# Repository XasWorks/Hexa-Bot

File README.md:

# Hexa-Bot

All required files, both .scad files for 3D Models aswell as the source files for the Arduino programming and the circuit plans for custom electronics (motor controller, special sensors, display etc.)

For documentation, see the "documentation" folder. Most importantly the scematics can be found under "KiCAD".

To program a robot, open Eclipse with working AVR Plugin, and "import existing project", with the folder being EclipseWS/Zephyr_Functional
The used PORTS can be changed inside the Code/System/Robot.h file.

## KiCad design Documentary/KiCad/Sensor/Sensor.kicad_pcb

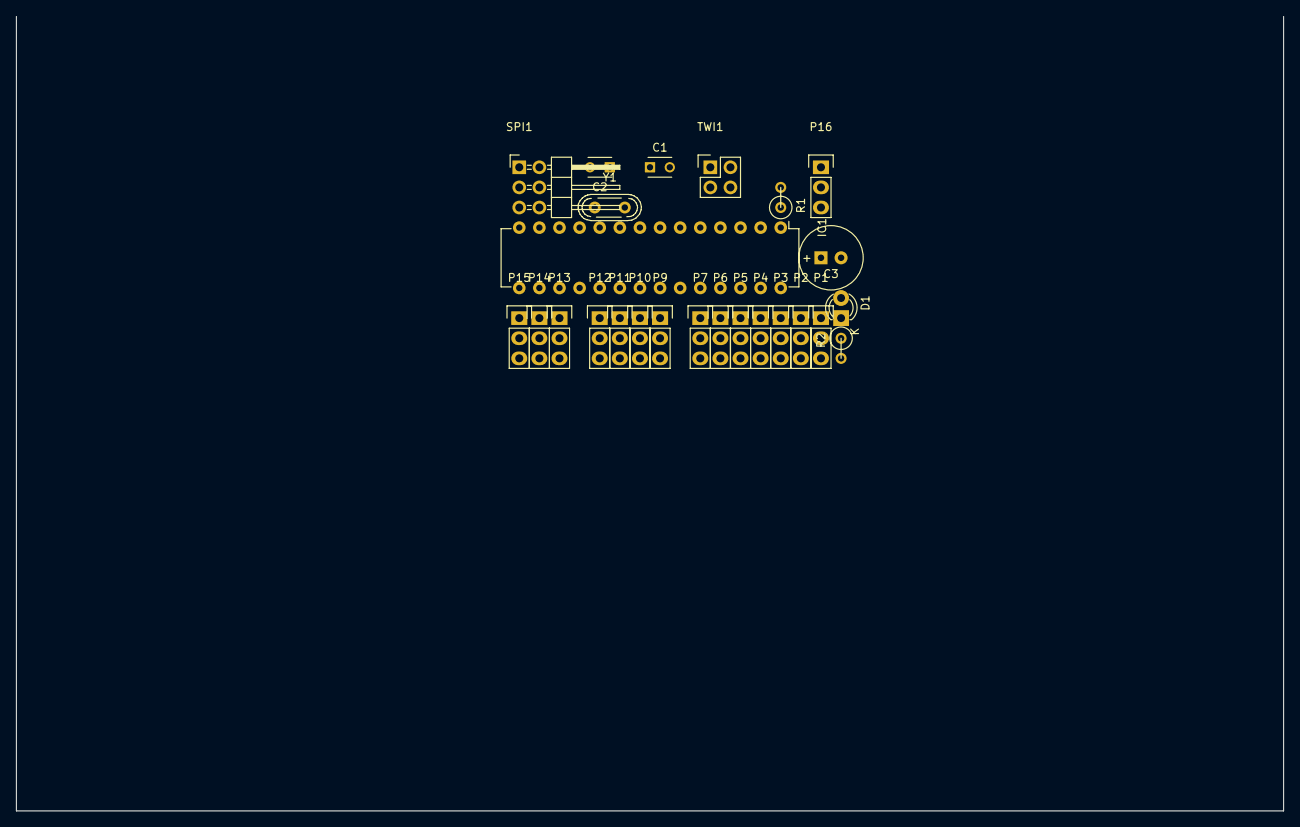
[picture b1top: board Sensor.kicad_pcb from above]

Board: 2 copper layers, 160.0 x 100.3 mm, 25 parts (0 on the bottom side), 26 nets, no tracks yet.

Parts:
C1, C2: C_Small; C_Disc_D3_P2.5
C3: CP; C1V8
D1: Led_Small; LED-3MM
IC1: ATMEGA8-P; DIP-28_W7.62mm
P1, P2, P3, P4, P5, P6, P7, P9, P10, P11, P12, P13, P14, P15, P16: CONN_01X03; Pin_Header_Straight_1x03
R1: R; R1
R2: R_Small; R1
SPI1: CONN_02X03; Pin_Header_Angled_2x03
TWI1: CONN_02X02; Pin_Header_Straight_2x02
Y1: Crystal; Crystal_HC52-U_Vertical

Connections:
+5V: C3.1, IC1.7, IC1.20, IC1.21, P1.2, P2.2, P3.2, P4.2, P5.2, P6.2, P7.2, P9.2, P10.2, P11.2, P12.2, P13.2, P14.2, P15.2, P16.2, R1.2, SPI1.2, TWI1.4
/MISO: IC1.18, SPI1.1
/MOSI: IC1.17, P16.1, SPI1.4
/PB0: IC1.14, P13.1
/PB1: IC1.15, P14.1
/PB2: IC1.16, P15.1
/PC0: IC1.23, P9.1
/PC1: IC1.24, P10.1
/PC2: IC1.25, P11.1
/PC3: IC1.26, P12.1
/PD0: IC1.2, P1.1
/PD1: IC1.3, P2.1
/PD2: IC1.4, P3.1
/PD3: IC1.5, P4.1
/PD4: IC1.6, P5.1
/PD5: IC1.11, P6.1
/PD6: IC1.12, P7.1
/PD7: D1.2, IC1.13
/RST: IC1.1, R1.1, SPI1.5
/SCK: IC1.19, SPI1.3
/SCL: IC1.28, TWI1.2
/SDA: IC1.27, TWI1.1
GND: C1.1, C2.2, C3.2, IC1.8, IC1.22, P1.3, P2.3, P3.3, P4.3, P5.3, P6.3, P7.3, P9.3, P10.3, P11.3, P12.3, P13.3, P14.3, P15.3, P16.3, R2.2, SPI1.6, TWI1.3
unnamed: C1.2, IC1.9, Y1.2
unnamed: C2.1, IC1.10, Y1.1
unnamed: D1.1, R2.1

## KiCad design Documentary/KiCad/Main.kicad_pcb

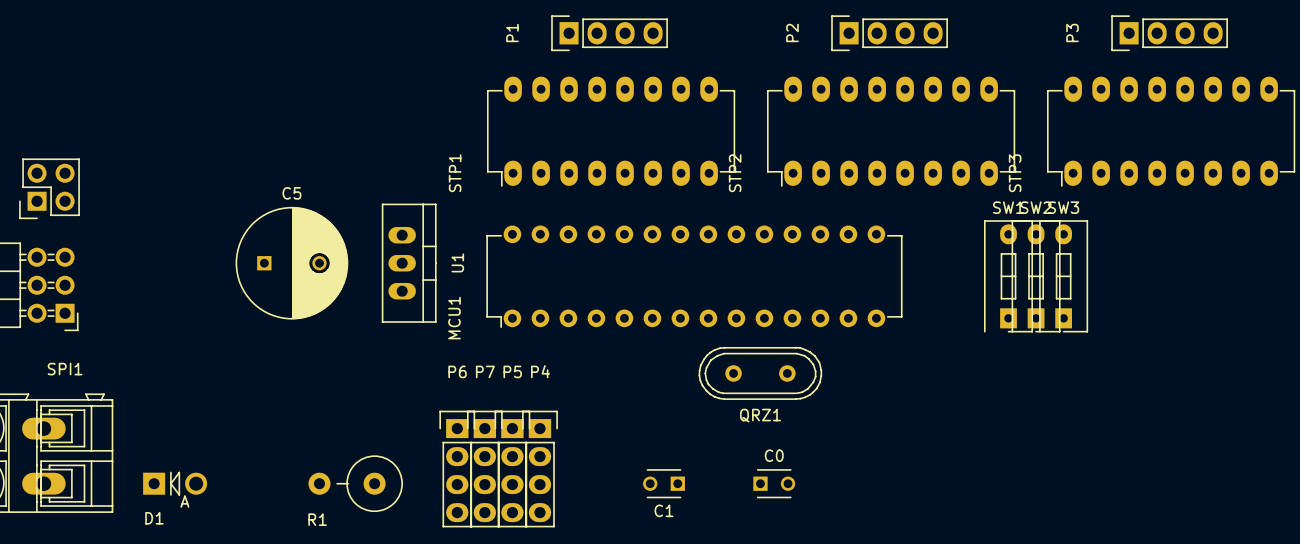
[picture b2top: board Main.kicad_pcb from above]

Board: 32 copper layers, 24 parts (0 on the bottom side), 40 nets, no tracks yet.

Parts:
C0, C1: C_Small; C_Disc_D3_P2.5
C5: CP; C_Radial_D10_L13_P5
D1: D_Small; Diode_DO-41_SOD81_Vertical_AnodeUp
MCU1: ATMEGA328-P; DIP-28_W7.62mm
P1, P2, P3: CONN_01X04; Pin_Header_Straight_1x04
P4, P5, P6, P7: CONN_01X03; Pin_Header_Straight_1x04
P8: CONN_02X02; Pin_Header_Straight_2x02
P9: CONN_01X02; AK300-2
QRZ1: Crystal; Crystal_HC49-U_Vertical
R1: 1M; Resistor_Vertical_RM5mm
SPI1: CONN_02X03; Pin_Header_Angled_2x03
STP1, STP2, STP3: A4988; DIP-16_W7.62mm_LongPads
SW1, SW2, SW3: SPST; SW_DIP_x1_Slide
U1: 7805; TO-220_Neutral123_Vertical

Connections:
+5V: C5.1, MCU1.7, MCU1.20, MCU1.21, P4.2, P5.2, P6.2, P7.2, P8.2, R1.2, SPI1.2, STP1.10, STP2.10, STP3.10, U1.3
+12V: P9.2, STP1.16, STP2.16, STP3.16, U1.1
/DR0: MCU1.3, STP1.8
/DR1: MCU1.5, STP2.8
/DR2: MCU1.11, STP3.8
/MISO: MCU1.18, SPI1.1
/MOSI: MCU1.17, SPI1.4
/MS0: STP1.2, STP2.2, STP3.2, SW1.2
/MS1: STP1.3, STP2.3, STP3.3, SW2.2
/MS2: STP1.4, STP2.4, STP3.4, SW3.2
/RST: MCU1.1, R1.1, SPI1.5
/SCK: MCU1.19, SPI1.3
/SCL: MCU1.28, P8.4
/SDA: MCU1.27, P8.3
/SN0: MCU1.23, P4.1
/SN1: MCU1.24, P5.1
/SN2: MCU1.25, P6.1
/SN3: MCU1.26, P7.1
/ST0: MCU1.2, STP1.7
/ST1: MCU1.4, STP2.7
/ST2: MCU1.6, STP3.7
GND: C0.1, C1.2, C5.2, D1.2, MCU1.8, MCU1.22, P4.3, P5.3, P6.3, P7.3, P8.1, SPI1.6, STP1.9, STP1.15, STP2.9, STP2.15, STP3.9, STP3.15, SW1.1, SW2.1, SW3.1, U1.2
unnamed: C0.2, MCU1.10, QRZ1.1
unnamed: C1.1, MCU1.9, QRZ1.2
unnamed: D1.1, P9.1
unnamed: P1.1, STP1.14
unnamed: P1.2, STP1.13
unnamed: P1.3, STP1.12
unnamed: P1.4, STP1.11
unnamed: P2.1, STP2.14
unnamed: P2.2, STP2.13
unnamed: P2.3, STP2.12
unnamed: P2.4, STP2.11
unnamed: P3.1, STP3.14
unnamed: P3.2, STP3.13
unnamed: P3.3, STP3.12
unnamed: P3.4, STP3.11
unnamed: STP1.5, STP1.6
unnamed: STP2.5, STP2.6
unnamed: STP3.5, STP3.6

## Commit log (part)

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2010-01-01 Changed drive preference to move along right, not left.
2015-09-16 Initial commit, the first HexGrid outline finished
2015-09-16 There we go. Actual Commit, including all the files (instead of empty push *sigh*)
2015-09-16 Removed that one weird HexGrid.scad directly in the master directory. Why.
2015-09-17 Added the first (and hopefully last) version of the .scad file used for creating the subwheels of a Omni-wheel. All functions are commented, no need for later commenting.
2015-09-17 Finalised version of the omni-wheel .scad!
2015-09-17 Fine-tuned the Filament-Axis holes.
    Values are now: 2.25 for tight-fitting and 2.4 for loosely-fitting.
2015-09-19 Filament axis hole now is only tighter towards end of the wheel.
    This should make it much more easy to insert the filament and fix the wheels in place. Glue is still recommended.
    Also, the hole diameter now is designed for toothpicks!!!
2015-09-20 Optimised and changed a few things.
    Nothing worth noting, mostly making the holes more fitting!
2015-09-20 Nearly done ...
2015-09-21 Finalised the alternate design!
    Added connectors for the subwheels, changed up the center piece a bit to use up less filament and all that.
2015-09-23 Complete redesign! My gosh, everything has changed. The central cylinder now is split into two symmetric parts that have to be glued together This SHOULD fix printing problems and allow for connector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
2015-09-25 Redid the Center piece code, much cleaner now.
    Redid lots of things, most noticably the center piece.
    This also includes stuff and configurability. Lots of things were replaced by variables and should be MUCH easier to configure now.
2015-09-26 Even more configurability! Seriously, round about now almost everything can be configured with a variable. //No warnings will be issued if the variables are set wrong!! //
2015-09-27 Added subwheel overlap value. This should allow for smoother running, as the subwheels overlap for a short amount of time, allowing the wheels to have a smoother run.
2015-10-01 First improvements on the Hexagonal Structure system!
    Made a few things accessible through variables, will change up the actual values and stuff later on.
2015-10-03 Added the eclipse workspace, and started LCD Driver!!
2015-10-04 Experimenting with C++ classes (LEDPWM)
    This first experiment is meant simply to test out a few things I want to have for a private, non-related project.
    However, the advances in understanding C++ will greatly help me out in continuing with this system.
2015-10-05 Ah ... Forgot the LED PWM Files
2015-10-06 Whoop Whoop, base stepper code fully functional!
    That is AWESOME, as now those dang steppers can be used perfectly!
    Also, the base frame code can easily be extended by overwriting the basic classes, or the stepper itself can be tested and moved about with the implemented function!
2015-10-07 Improvements to the ISR Step speed calculation.
    I still have to play around with the system to find out the best way to calculate and step the motors.
    Right now it fails to go over a specific amount (ISR Frequency < Stepping speed), but this can be resolved by making the ISR faster.
2015-10-08 First tries for accelleration!
2015-10-08 First complex driver motor calculation classes.
    And it already supports moving itself a specified amount of steps!!
2015-10-08 Some last minute testing and messing around.
2015-10-15 Untested optimisations for mov. cal and refined and strenghtened OmniWheel Bases.
2015-10-24 Small fix for the Stepper Motor connecting plate (size)
2015-10-25 Fixes to the new hexgrid system
2015-11-10 Start of code rewrite, implementation of interface "Movable"
2015-11-10 Commenting for class "Movable"
2015-11-15 Finished the last elemets of the new stepper system.
2015-11-16 Moved all the important movement files to a separate folder.
2015-11-17 First implementations of the I2C important buffers
2015-11-19 Began redesigning the motor hex system, added base-plate with integrated motor holder.
2015-11-21 Tried to fix the hexGrid system, and kinda managed that + First attempt at the base plate.
2015-11-21 Comments. Lots of them. And a clearer, cleaner code. Finally.
2015-11-22 Small fixes to the stepper motor system.
2015-11-22 Final changes to the Hex Grid structure!
2015-11-22 Small tweaks to the OmniWheel
2015-11-23 Tiny fine-tuning to the Omniwheels
2015-11-27 Small important fix to the XY-Coordinate to TranslativeStepper-Coordinate calculation
2015-11-27 Small in-between test
2015-11-27 Final commit before merge
2015-11-28 Repositioned the NewHexGrid library
2015-12-02 Small tweaks to the distancer
2015-12-03 Added a LF Sensor mount for the System.
2015-12-05 Implementation of a electronics holder and other various fixes
2015-12-08 Interim commit before master merge
2015-12-08 Cleanup of .gitignore Files.
2015-12-09 Correcting some small values
2015-12-11 Final tweaks to the LF-Shielding
2015-12-12 Small tweak for the sensors (Scaling)
2015-12-13 +Smaller fixes +Added comments and port specifications -Deleted led support (cleaned up)
2015-12-14 Implementation of I2CJobs
2015-12-15 First attempts towards I2CJob
2015-12-16 Small tweaks to the LF
2015-12-20 v0.1 I2C - Master only!
2016-01-03 First verion of a proper LF Class This new class system should make working with Line Following much easier, as the interfacing functions will always stay the same. This allows for more changes to be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
2016-01-03 +Added the colour black to the programm *Tweaked the other colours a little to avoid overlapping
2016-01-05 Removal of unnececary project
2016-01-07 Addition of Updating change debuff and Intersection recognition.
2016-01-09 Added some commenting and code cleanup
2016-01-11 Complete project cleanup + main.cpp template (documentary)
2016-01-11 Moved all the init code and handling to new Robot class, yay!
2016-01-13 Changed the acceleration system to not immediately stop
2016-01-13 Inbetween commit - No idea what's going on.
2016-01-13 Removed most unnececary 'volatile' keywords
2016-01-14 Final changes and tweaks to the code.
2016-01-15 Added a 'Modules' System to make robot workflow even easier! :D
2016-01-25 Changed to function pointer use
2016-01-25 Implemented 'virtual' keywords to 'Updatable' and 'Movable'
2016-02-03 Value tweaking and minor code fixing
2016-02-03 Starting tweaks to find BUG 'SUDDEN STOP'
2016-02-03 Secured speed setting to not 0, reduced drive speed.
2016-02-06 Final small tweaks to the new holder
2016-02-07 Started working on refined I2C System
2016-02-07 Removed 'Mode' Variable from the I2C System
2016-02-08 Started design for a touch sensor mount :3
2016-02-09 Added the Object Avoidance module, yay! :D
2016-02-10 Tweaked the 'isReady()' behavior
2016-02-10 Added Y movement rotation compensation value
2016-02-13 Added the technical documentation of the robot. Yay! :D
2016-02-16 Added the object avoidance into normal code sequence!
2016-02-17 Finalised the robot code phase one!
2016-02-19 Added the KiCad project folder (scematics)
2016-02-19 Finalised the scematics, and started working on a PCB!
2016-02-20 First attempts at making a PCB!
2016-02-20 Added a PDF of main scematic for Sparkly!
2016-02-22 Tweaking for gluestrips.
2016-02-22 First implementation of the advanced intsec code.
2016-02-22 Added break-out code in case of false activation
2016-02-22 Tuned backoff abort distance and forwards movement.
2016-02-22 Small tweak to the code exectuion order.
2016-02-23 Speed adjustment for going up the ramp!
2016-02-23 More value tweaking! :3
2016-02-23 Speed reduction + rotation acceleration
2016-02-23 Ensured proper intersection detection
2016-02-23 Changed Intersection code to default move towards the left!
2016-02-23 Started working on #Hotfix sensor :3
2016-02-23 Adding more functions for the reading sensor!
2016-02-23 Began implementation of the sensor
2016-02-23 Added Intersection forwards movement again.
2016-02-24 Removed external intsec detection.
2016-02-24 Added first version of a grabbing arm! :D
2016-02-26 Added 3D Model for the moving arm part.
2016-02-26 Changed some rendering scene related things :3
2016-02-27 Filled out the hexes for the arm mount.
2016-02-29 Began total redo of TWI System.
2016-02-29 Added default handing functions to TWI_Basic
    These simple functions currently only allow for sending messages. Receiving yet to be supported.
2016-02-29 Began implementation of new TWI Job systems, with working static pointer chain system.
2016-02-29 Further enhancements of the sensor plate.
2016-03-01 Added 'Return status' function and status variable.
2016-03-02 Added basic structure for a slave handler.
    The slave handler TWI Job has the same basic structure.
    However, purposes for the "begin" and "end" functions will be different.
    A slave job's "begin" function will be called upon receival of the own SLA+R code (Slave transmit), letting the job load in data to send.
    A slave job's "end" function will be called after a successful SLA+W (Slave read) data transfer, to let the job handle the data.
2016-03-02 Ensured that the default 'nextNode' equals 0 unless set.
2016-03-02 Added speed setting. No proper speed support yet!
2016-03-07 Changed the searchJobs() function to now also automatically execute the job. Needs testing.
2016-03-08 Fixed a bug in the 'searchJobs' func. TWI now tested & MT works.
2016-03-12 Began /actual/ work on the sensor kit.
2016-03-12 Fixed the TWI connections.
2016-03-14 Added some .gitignore files
2016-03-16 Lots of new status codes
2016-03-16 Implementation of the Slave-Transmit and Slave Receive modes.
2016-03-16 Adjusted 'endJob()' to fit new 'searchJobs()' behavior
2016-03-17 Renamed searchJobs to searchMasterJobs
2016-03-17 Added a TWI_S_Job class!
2016-03-17 Forget everything ;-; This reverts commit 1392298a5fbaf5fdffb083e8442a70ad5c44f210.
2016-03-17 Added proper slave job integration into the handler.
2016-03-18 Added an 'updateJobs' function for the TWI_Handler to search for new TWI jobs
2016-03-18 Implemented somewhat proper handling for the onError function within TWI_Handler
2016-03-23 Fixed proper PORTC output setting on the TWI Basic initialisation.
2016-03-23 Added a small ball ring to place it on.
2016-03-23 Removed debug lights.
2016-04-03 Small name-change from 'port' to 'pin' and addition of a 'measure' function (pausing)
2016-04-11 Addition of the IR distance sensor chip!
2016-04-12 Completed TIMER1 CTC mode & added proper distance calculation for the IRDistSensor update
2016-04-12 Small distance tweak to improve mesh-manifoldness
2016-04-13 Split the IRDistSensor update function into a update() and adc_update(), to not block Timer1 ISR.
2016-04-16 Forgot to add the IRDistanceSensor files.
2016-04-16 First working data communication between MCU and SENSR
2016-04-17 Re-Added delay, as coms still seemed to block.
2016-04-18 Removed RotationPerY compensation value! (Not good for finer movements that already compensate properly).
2016-04-18 Removed the delay after irdist.update(); it is not required any longer!
2016-04-19 Begun adding a new 'subspace' system that will properly take care of moving within a 'shifted' frame of reference.
2016-04-20 Added a first layout of a fine-tuned ball grabbing function :3
2016-04-22 Added setting the readLength variable, instead of reading in 255 bytes X3
2016-04-23 Added a holder for the Grayscale sensor!
2016-04-23 Ball grabbing/kicking sequence v2 commit!
2016-04-23 Added a new Coms codes, as well as the slave version of brightness sensor.
2016-04-23 Actually implementing the Brightness Sensor into the SensorChip code.
2016-04-25 Fixed ADC_Lib 'selectNextPin()' function
2016-04-25 Changed BrightnessSensor (MR) to receive a 16-Bit value
2016-04-26 Added a brightness sensor shielding!
2016-04-27 Fixed setting the touch sensor as output, thusly reduces heating
2016-04-27 Added a middle light blockade to prevent self-lighting issues and made walls thicker.
2016-04-27 Added a 3D-Printed QR-Code! Don't ask :P
2016-04-28 Made the sensor mounts a tiny bit more sturdy, and more pretty.
2016-04-28 Debugging of the brightness sensor detection sensitivity
2016-04-28 Random stuff.
2016-04-29 Made the intersection code count the intersections.
2016-04-29 Forgot to make the array a /signed/ one.
2016-04-29 Reverting the removal of the compesation values
2016-04-29 Preparing the robot for the second run.
2016-04-29 Returned DEFAULT_DIR to right-facing, not left-facing
2016-04-30 Tweaked system for the next course.
2016-04-30 Added a variable-direction object avoiding code.
2016-04-30 Implemented the changes
